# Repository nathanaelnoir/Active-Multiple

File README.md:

# Active Multiple

Active Multiple — a compact active buffered multiple for Eurorack modular synths.

## Contents

- Overview
- Features
- Quick start (KiCad 9)
- Files
- Build & assembly notes
- Testing
- High-level BOM
- License & contributing

## Overview

This repository holds the KiCad 9 project for an active multiple (buffered split). Designed by Dirty Dream — Nathanael Noir — the module accepts audio/CV inputs and provides low-impedance buffered outputs so signals can be split without loading downstream modules.

## Features

- Two independent channels (A & B).
- Per-channel quad buffering using TL074 op-amps (low-noise JFET-input quads).
- 3.5 mm TS jacks (QingPu / Thonkiconn footprint).
- Standard Eurorack power: +12 V / -12 V / GND via a 2x5 (10-pin) header.
- Mostly SMD (surface-mount) components; through-hole only for audio jacks and the Eurorack power header. Assembly is a mixed SMD + THT workflow.

## Quick start

1. Install KiCad 9 (this project was created/edited in KiCad 9).
2. Open the project: `kicad/buffer-module.kicad_pro`.
3. Inspect sheets and ERC, then run CV/PWR checks before exporting fabrication files.

## Files

- `kicad/buffer-module.kicad_sch` — top-level schematic (multi-sheet)
- `kicad/quad buffer.kicad_sch` — quad-buffer sheet (re-used per channel)
- `kicad/Europower +12 -12 GND.kicad_sch` — Eurorack power header sheet
- `kicad/buffer-module.kicad_pcb` — PCB
- `kicad/buffer-module.kicad_pro` — KiCad project file

Note: there is a single PCB layout file (`kicad/buffer-module.kicad_pcb`) for this project.

## Build & assembly notes

- Populate the PCB according to the schematic. Observe TL074 pin-1 orientation.
- Typical footprints:
	- Audio jacks: `AudioJacks2:Jack_3.5mm_QingPu_WQP-PJ398SM_Vertical` (vertical Thonkiconn-style)
	- Power connector: 2x5 Eurorack header (standard 10-pin)
- Add local decoupling (100 nF) on each op-amp power pin pair and bulk caps on rails.
- Double-check power-header orientation with your case header before applying power.

## Testing

1. With no inputs connected, power up and verify rails (+12 V / -12 V) at op-amp supply pins.
2. Feed a low-frequency sine into `Input A` and verify the outputs `OutA/OutB/OutC/OutD` reproduce it cleanly.
3. Connect multiple outputs to confirm splitting works without distortion or level loss.

## High-level BOM

- U1, U2 — TL074 (or compatible quad op-amp)
- J1..J9 — 3.5 mm TS jacks (vertical Thonkiconn/QingPu)
- Jpwr — 2x5 Eurorack power connector
- Resistors, caps, and decoupling components — see schematic for values and placement

For a detailed BOM, use KiCad's BOM export or ask me to generate a CSV from the project files.

### Bill of Materials (detailed)

| Designator(s) | Qty | Value / Part | Footprint | Datasheet |
|---|---:|---|---|---|
| C1, C2 | 2 | 10 µF | Capacitor_SMD:CP_Elec_5x5.4 | [datasheet](https://www.taydaelectronics.com/datasheets/files/a-1677.pdf) |
| C3–C8 | 6 | 100 nF | Capacitor_SMD:C_0805_2012Metric_Pad1.18x1.45mm_HandSolder | [datasheet](https://www.taydaelectronics.com/100nf-50v-smd-ceramic-chip-capacitor.html) |
| D1 | 1 | LED_Dual_A (bi-color) | LED_THT:LED_D3.0mm | [product](https://www.taydaelectronics.com/bi-color-led-3mm-red-green.html) |
| D2 | 1 | LED_Dual_B (bi-color) | LED_THT:LED_D3.0mm | [product](https://www.taydaelectronics.com/bi-color-led-3mm-red-green.html) |
| FB1, FB2 | 2 | Ferrite bead (small) | Inductor_SMD:L_0805_2012Metric_Pad1.05x1.20mm_HandSolder | [datasheet](https://www.taydaelectronics.com/datasheets/files/A-3191.PDF) |
| J1 | 1 | Jack_InA (3.5 mm TS) | AudioJacks2:Jack_3.5mm_QingPu_WQP-PJ398SM_Vertical | [datasheet](https://www.taydaelectronics.com/datasheets/files/w-qp-518ma_drawings.pdf) |
| J2 | 1 | Jack_InB (3.5 mm TS) | AudioJacks2:Jack_3.5mm_QingPu_WQP-PJ398SM_Vertical | [datasheet](https://www.taydaelectronics.com/datasheets/files/w-qp-518ma_drawings.pdf) |
| J3 | 1 | Jack_OutA-1 (3.5 mm TS) | AudioJacks2:Jack_3.5mm_QingPu_WQP-PJ398SM_Vertical | [datasheet](https://www.taydaelectronics.com/datasheets/files/w-qp-518ma_drawings.pdf) |
| J4 | 1 | Jack_OutA-2 (3.5 mm TS) | AudioJacks2:Jack_3.5mm_QingPu_WQP-PJ398SM_Vertical | [datasheet](https://www.taydaelectronics.com/datasheets/files/w-qp-518ma_drawings.pdf) |
| J5 | 1 | Jack_OutA-3 (3.5 mm TS) | AudioJacks2:Jack_3.5mm_QingPu_WQP-PJ398SM_Vertical | [datasheet](https://www.taydaelectronics.com/datasheets/files/w-qp-518ma_drawings.pdf) |
| J6 | 1 | Jack_OutB-1 (3.5 mm TS) | AudioJacks2:Jack_3.5mm_QingPu_WQP-PJ398SM_Vertical | [datasheet](https://www.taydaelectronics.com/datasheets/files/w-qp-518ma_drawings.pdf) |
| J7 | 1 | Jack_OutB-2 (3.5 mm TS) | AudioJacks2:Jack_3.5mm_QingPu_WQP-PJ398SM_Vertical | [datasheet](https://www.taydaelectronics.com/datasheets/files/w-qp-518ma_drawings.pdf) |
| J8 | 1 | Jack_OutB-3 (3.5 mm TS) | AudioJacks2:Jack_3.5mm_QingPu_WQP-PJ398SM_Vertical | [datasheet](https://www.taydaelectronics.com/datasheets/files/w-qp-518ma_drawings.pdf) |
| J9 | 1 | Conn_02x05_Odd_Even (Eurorack power header) | Connector_IDC:IDC-Header_2x05_P2.54mm_Vertical | [datasheet](https://www.taydaelectronics.com/datasheets/files/A-2939.pdf) |
| R1, R6 | 2 | 1 MΩ | Resistor_SMD:R_0805_2012Metric_Pad1.20x1.40mm_HandSolder | [SMD info](https://www.taydaelectronics.com/datasheets/files/SMD.pdf) |
| R2–R4, R7–R9 | 6 | 1 kΩ | Resistor_SMD:R_0805_2012Metric_Pad1.20x1.40mm_HandSolder | [SMD info](https://www.taydaelectronics.com/datasheets/files/SMD.pdf) |
| R5, R10 | 2 | 300 Ω | Resistor_SMD:R_0805_2012Metric_Pad1.20x1.40mm_HandSolder | [SMD info](https://www.taydaelectronics.com/datasheets/files/SMD.pdf) |
| TP1–TP3 | 3 | TestPoint | TestPoint:TestPoint_Pad_D1.5mm | ~ |
| U1, U2 | 2 | TL074 (quad op-amp) | Package_SO:SOIC-14_3.9x8.7mm_P1.27mm | [datasheet](https://www.taydaelectronics.com/datasheets/files/A-1137.PDF) |

## License & contributing

This repository is released under the MIT license. See `LICENSE` for full text.

Contributions, issues, and pull requests welcome. If you publish PCBs or panels based on this design, please credit the original author: Dirty Dream — Nathanael Noir.

---

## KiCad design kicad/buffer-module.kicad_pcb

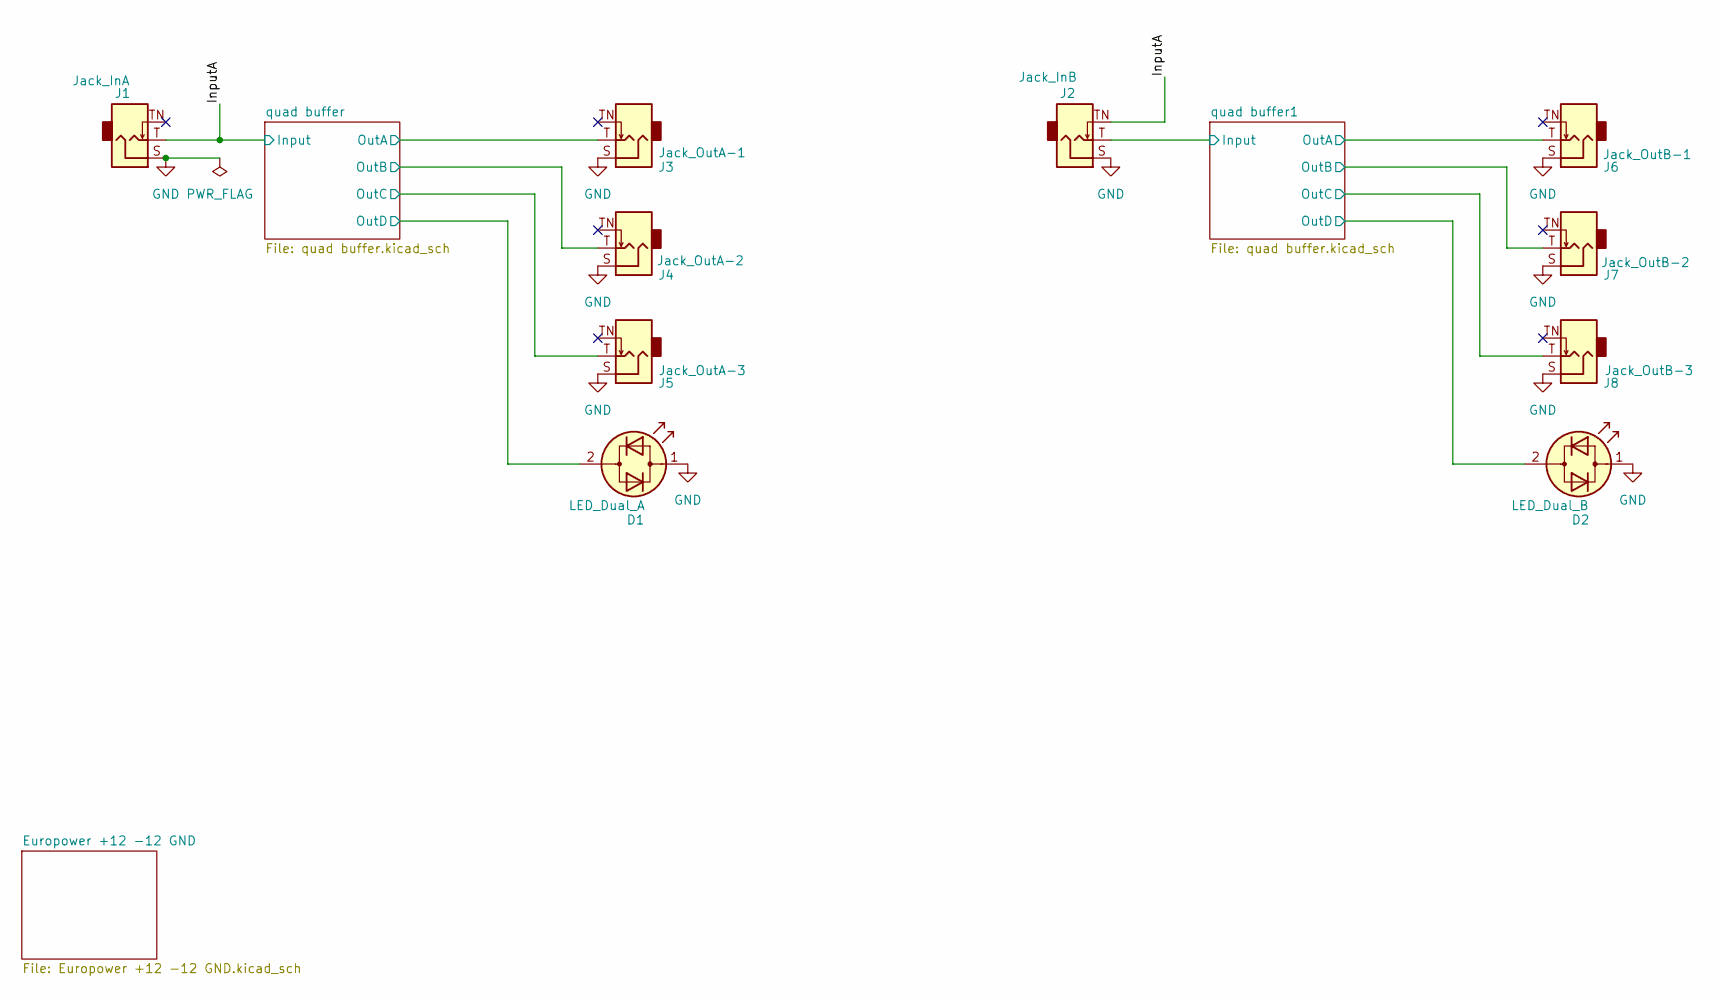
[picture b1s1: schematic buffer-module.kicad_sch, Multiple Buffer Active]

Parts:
D1: LED_Dual_A; LED_D3.0mm
D2: LED_Dual_B; LED_D3.0mm
J1: Jack_InA; Jack_3.5mm_QingPu_WQP-PJ398SM_Vertical
J2: Jack_InB; Jack_3.5mm_QingPu_WQP-PJ398SM_Vertical
J3: Jack_OutA-1; Jack_3.5mm_QingPu_WQP-PJ398SM_Vertical
J4: Jack_OutA-2; Jack_3.5mm_QingPu_WQP-PJ398SM_Vertical
J5: Jack_OutA-3; Jack_3.5mm_QingPu_WQP-PJ398SM_Vertical
J6: Jack_OutB-1; Jack_3.5mm_QingPu_WQP-PJ398SM_Vertical
J7: Jack_OutB-2; Jack_3.5mm_QingPu_WQP-PJ398SM_Vertical
J8: Jack_OutB-3; Jack_3.5mm_QingPu_WQP-PJ398SM_Vertical

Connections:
/InputA: J1.T, J2.TN; also elsewhere on the board
/quad buffer1/Input: J2.T; also elsewhere on the board
/quad buffer1/OutA: J6.T; also elsewhere on the board
/quad buffer1/OutB: J7.T; also elsewhere on the board
/quad buffer1/OutC: J8.T; also elsewhere on the board
/quad buffer1/OutD: D2.2 (AK); also elsewhere on the board
/quad buffer/OutA: J3.T; also elsewhere on the board
/quad buffer/OutB: J4.T; also elsewhere on the board
/quad buffer/OutC: J5.T; also elsewhere on the board
/quad buffer/OutD: D1.2 (AK); also elsewhere on the board
GND: D1.1 (KA), D2.1 (KA), J1.S, J2.S, J3.S, J4.S, J5.S, J6.S, J7.S, J8.S; also elsewhere on the board

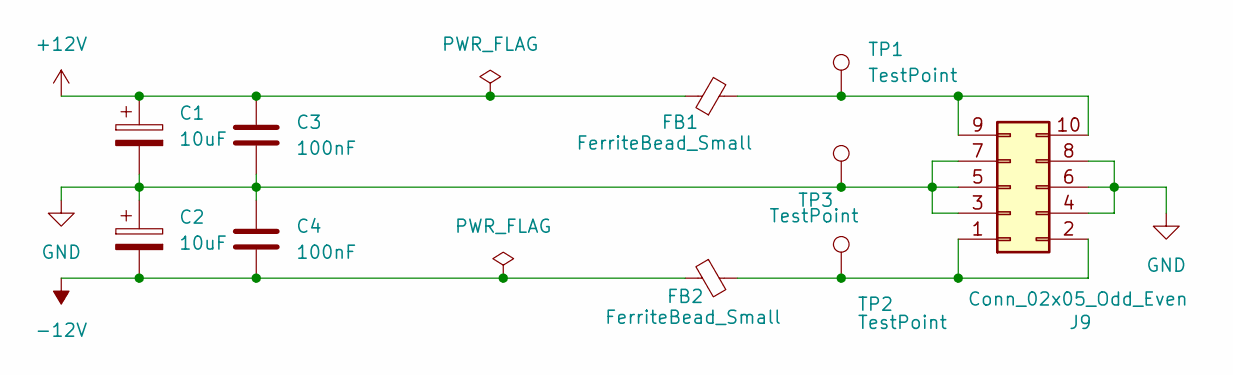
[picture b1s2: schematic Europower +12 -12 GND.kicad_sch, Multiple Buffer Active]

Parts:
C1, C2: 10uF; CP_Elec_5x5.4
C3, C4: 100nF; C_0805_2012Metric_Pad1.18x1.45mm_HandSolder
FB1, FB2: FerriteBead_Small; L_0805_2012Metric_Pad1.05x1.20mm_HandSolder
J9: Conn_02x05_Odd_Even; IDC-Header_2x05_P2.54mm_Vertical
TP1, TP2, TP3: TestPoint; TestPoint_Pad_D1.5mm

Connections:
+12V: C1.1, C3.1, FB1.1; also elsewhere on the board
-12V: C2.2, C4.2, FB2.1; also elsewhere on the board
GND: C1.2, C2.1, C3.2, C4.1, J9.3, J9.4, J9.5, J9.6, J9.7, J9.8, TP3.1; also elsewhere on the board
unnamed 13: FB2.2, J9.1, J9.2, TP2.1; also elsewhere on the board
unnamed 14: FB1.2, J9.9, J9.10, TP1.1; also elsewhere on the board

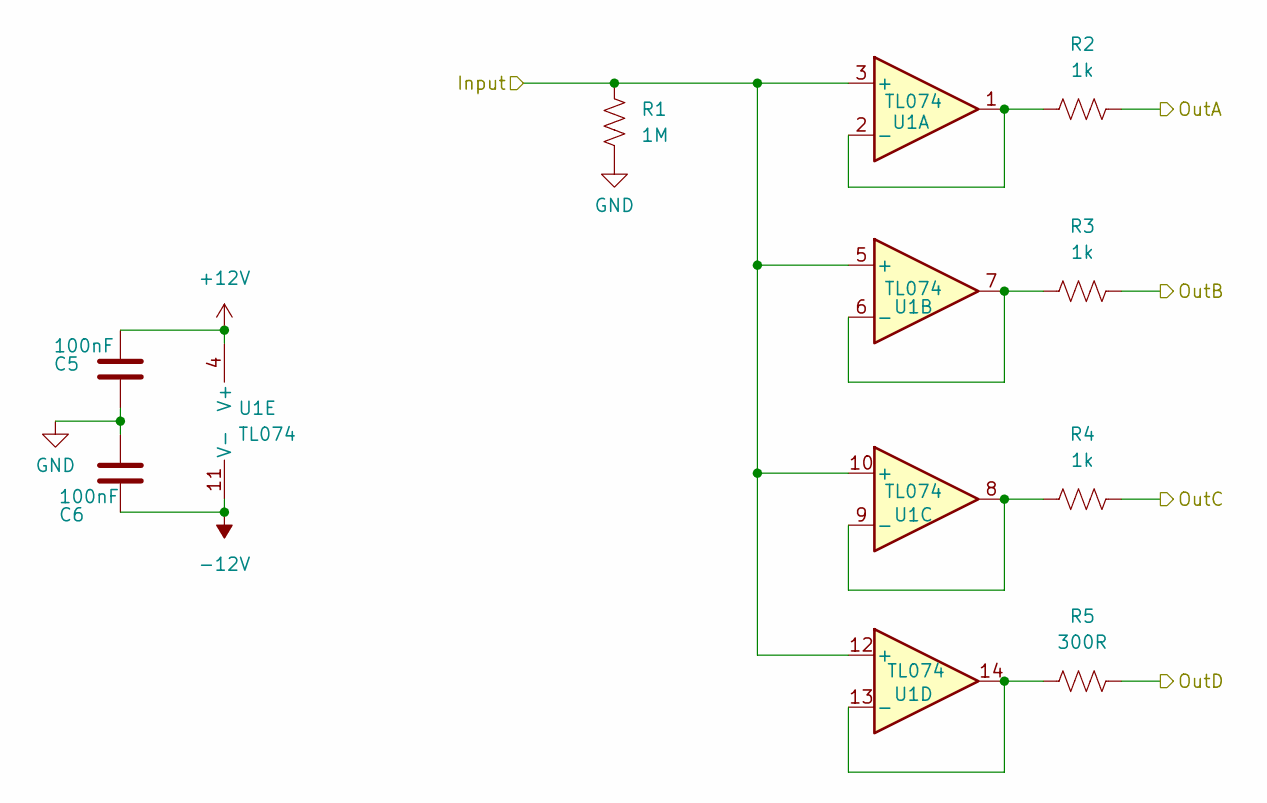
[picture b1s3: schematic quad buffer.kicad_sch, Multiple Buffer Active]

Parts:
C5, C6: 100nF; C_0805_2012Metric_Pad1.18x1.45mm_HandSolder
R1: 1M; R_0805_2012Metric_Pad1.20x1.40mm_HandSolder
R2, R3, R4: 1k; R_0805_2012Metric_Pad1.20x1.40mm_HandSolder
R5: 300R; R_0805_2012Metric_Pad1.20x1.40mm_HandSolder
U1: TL074; SOIC-14_3.9x8.7mm_P1.27mm

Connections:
+12V: C5.1, U1.4 (V+); also elsewhere on the board
-12V: C6.2, U1.11 (V-); also elsewhere on the board
/InputA: R1.2, U1.3 (+), U1.5 (+), U1.10 (+), U1.12 (+); also elsewhere on the board
/quad buffer/OutA: R2.2; also elsewhere on the board
/quad buffer/OutB: R3.2; also elsewhere on the board
/quad buffer/OutC: R4.2; also elsewhere on the board
/quad buffer/OutD: R5.1; also elsewhere on the board
GND: C5.2, C6.1, R1.1; also elsewhere on the board
unnamed: R2.1, U1.1, U1.2 (-)
unnamed: R3.1, U1.6 (-), U1.7
unnamed: R4.1, U1.8, U1.9 (-)
unnamed: R5.2, U1.13 (-), U1.14

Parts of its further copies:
C7, C8: 100nF; C_0805_2012Metric_Pad1.18x1.45mm_HandSolder
R6: 1M; R_0805_2012Metric_Pad1.20x1.40mm_HandSolder
R7, R8, R9: 1k; R_0805_2012Metric_Pad1.20x1.40mm_HandSolder
R10: 300R; R_0805_2012Metric_Pad1.20x1.40mm_HandSolder
U2: TL074; SOIC-14_3.9x8.7mm_P1.27mm

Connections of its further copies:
+12V: C7.1, U2.4 (V+); also elsewhere on the board
-12V: C8.2, U2.11 (V-); also elsewhere on the board
/quad buffer1/Input: R6.2, U2.3 (+), U2.5 (+), U2.10 (+), U2.12 (+); also elsewhere on the board
/quad buffer1/OutA: R7.2; also elsewhere on the board
/quad buffer1/OutB: R8.2; also elsewhere on the board
/quad buffer1/OutC: R9.2; also elsewhere on the board
/quad buffer1/OutD: R10.1; also elsewhere on the board
GND: C7.2, C8.1, R6.1; also elsewhere on the board
unnamed: R7.1, U2.1, U2.2 (-)
unnamed: R8.1, U2.6 (-), U2.7
unnamed: R9.1, U2.8, U2.9 (-)
unnamed: R10.2, U2.13 (-), U2.14

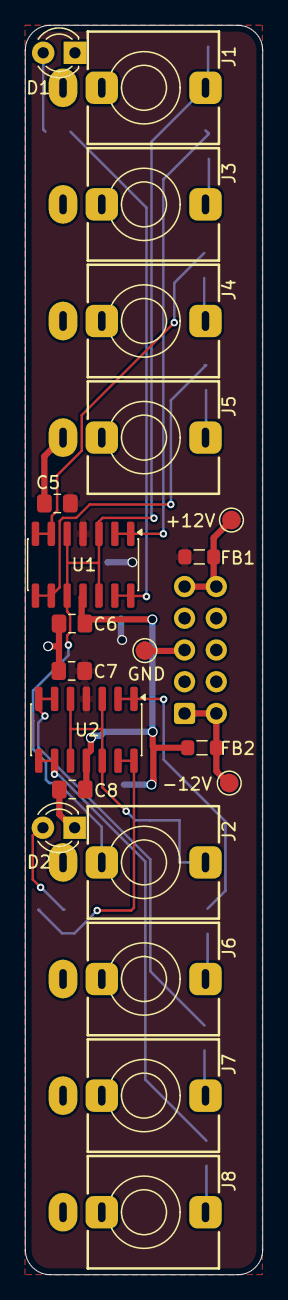
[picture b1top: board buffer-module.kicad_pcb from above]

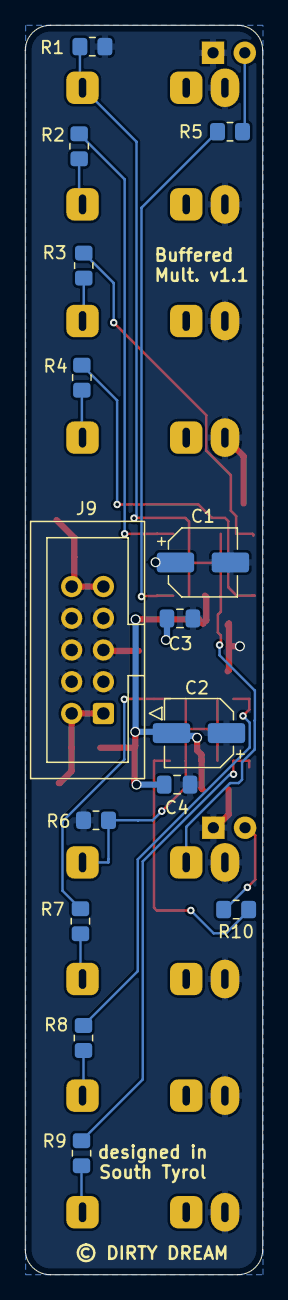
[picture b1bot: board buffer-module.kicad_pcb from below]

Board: 2 copper layers, 19.0 x 100.0 mm, 36 parts (15 on the bottom side), 23 nets.

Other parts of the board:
+12V: TestPoint; TestPoint_Pad_D1.5mm
-12V: TestPoint; TestPoint_Pad_D1.5mm
GND: TestPoint; TestPoint_Pad_D1.5mm

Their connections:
GND: GND.1; also elsewhere on the board
unnamed 13: -12V.1; also elsewhere on the board
unnamed 14: +12V.1; also elsewhere on the board

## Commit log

2026-02-10 Add project title and description to README
2026-02-11 modifying the .gitignore
2026-02-11 chore: clean up empty code change sections in the changes log
2026-02-11 Refactor code structure for improved readability and maintainability
2026-02-11 Enhance README with detailed project overview, features, specifications, testing instructions, and licensing information
2026-02-11 Add MIT license file to the repository
2026-02-11 Update README with additional badges and clarify assembly component types
2026-02-11 Remove outdated note about Instagram follower-count badge from README
2026-02-11 Reorder badge display in README for improved clarity
2026-02-11 Reposition project title in README for improved visibility
2026-02-11 Add initial KiCad project files for buffer module
    - Created buffer-module.kicad_prl with board settings, visibility options, and net inspector panel configurations.
    - Added lock file ~buffer-module.kicad_sch.lck to track user session information.
2026-02-11 Add footprint for Jack 3.5mm QingPu WQP-PJ398SM Vertical mount
2026-02-11 Refactor buffer-module: Remove unused silk layers and update footprint references
    - Removed multiple unused silk layer entries from buffer-module.kicad_pro to clean up the design.
    - Updated footprint references in buffer-module.kicad_sch from "AudioJacks2" to "Eurorack" for consistency across the schematic.
    - Deleted the lock file ~buffer-module.kicad_sch.lck as it is no longer needed.
2026-02-12 Refactor KiCad project files for improved layout and organization
    - Adjusted column widths in buffer-module.kicad_prl for better readability.
    - Cleared unnecessary DRC exclusions in buffer-module.kicad_pro to streamline design rules.
    - Updated sheet positions and properties in buffer-module.kicad_sch for enhanced clarity.
    - Realigned junctions and wires in quad buffer schematic for improved circuit flow and readability.
    - Corrected component positions and properties in quad buffer schematic to ensure accurate representation.
2026-02-12 Update README.md: Enhance badge section and add note on PCB layout file
2026-02-12 adding Gerber files
2026-02-12 zipping Gerber files
2026-02-13 change of text
2026-02-13 changing .gitignore
2026-02-13 docs: add CONTRIBUTING.md with KiCad contribution workflow and PR checklist
2026-02-13 removing autogenerated file
2026-03-08 docs: add changelog and document v1.1 test point rename
    - Added Changelog section to README
    - Documented v1.1 schematic update (test point names aligned with power rails)
    - Noted that v1.0 boards were manufactured and tested successfully
2026-03-08 docs: replace Orb Vision badge in README

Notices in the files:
README.md:
License: MIT
kicad/buffer-module.kicad_pcb:
© DIRTY DREAM
